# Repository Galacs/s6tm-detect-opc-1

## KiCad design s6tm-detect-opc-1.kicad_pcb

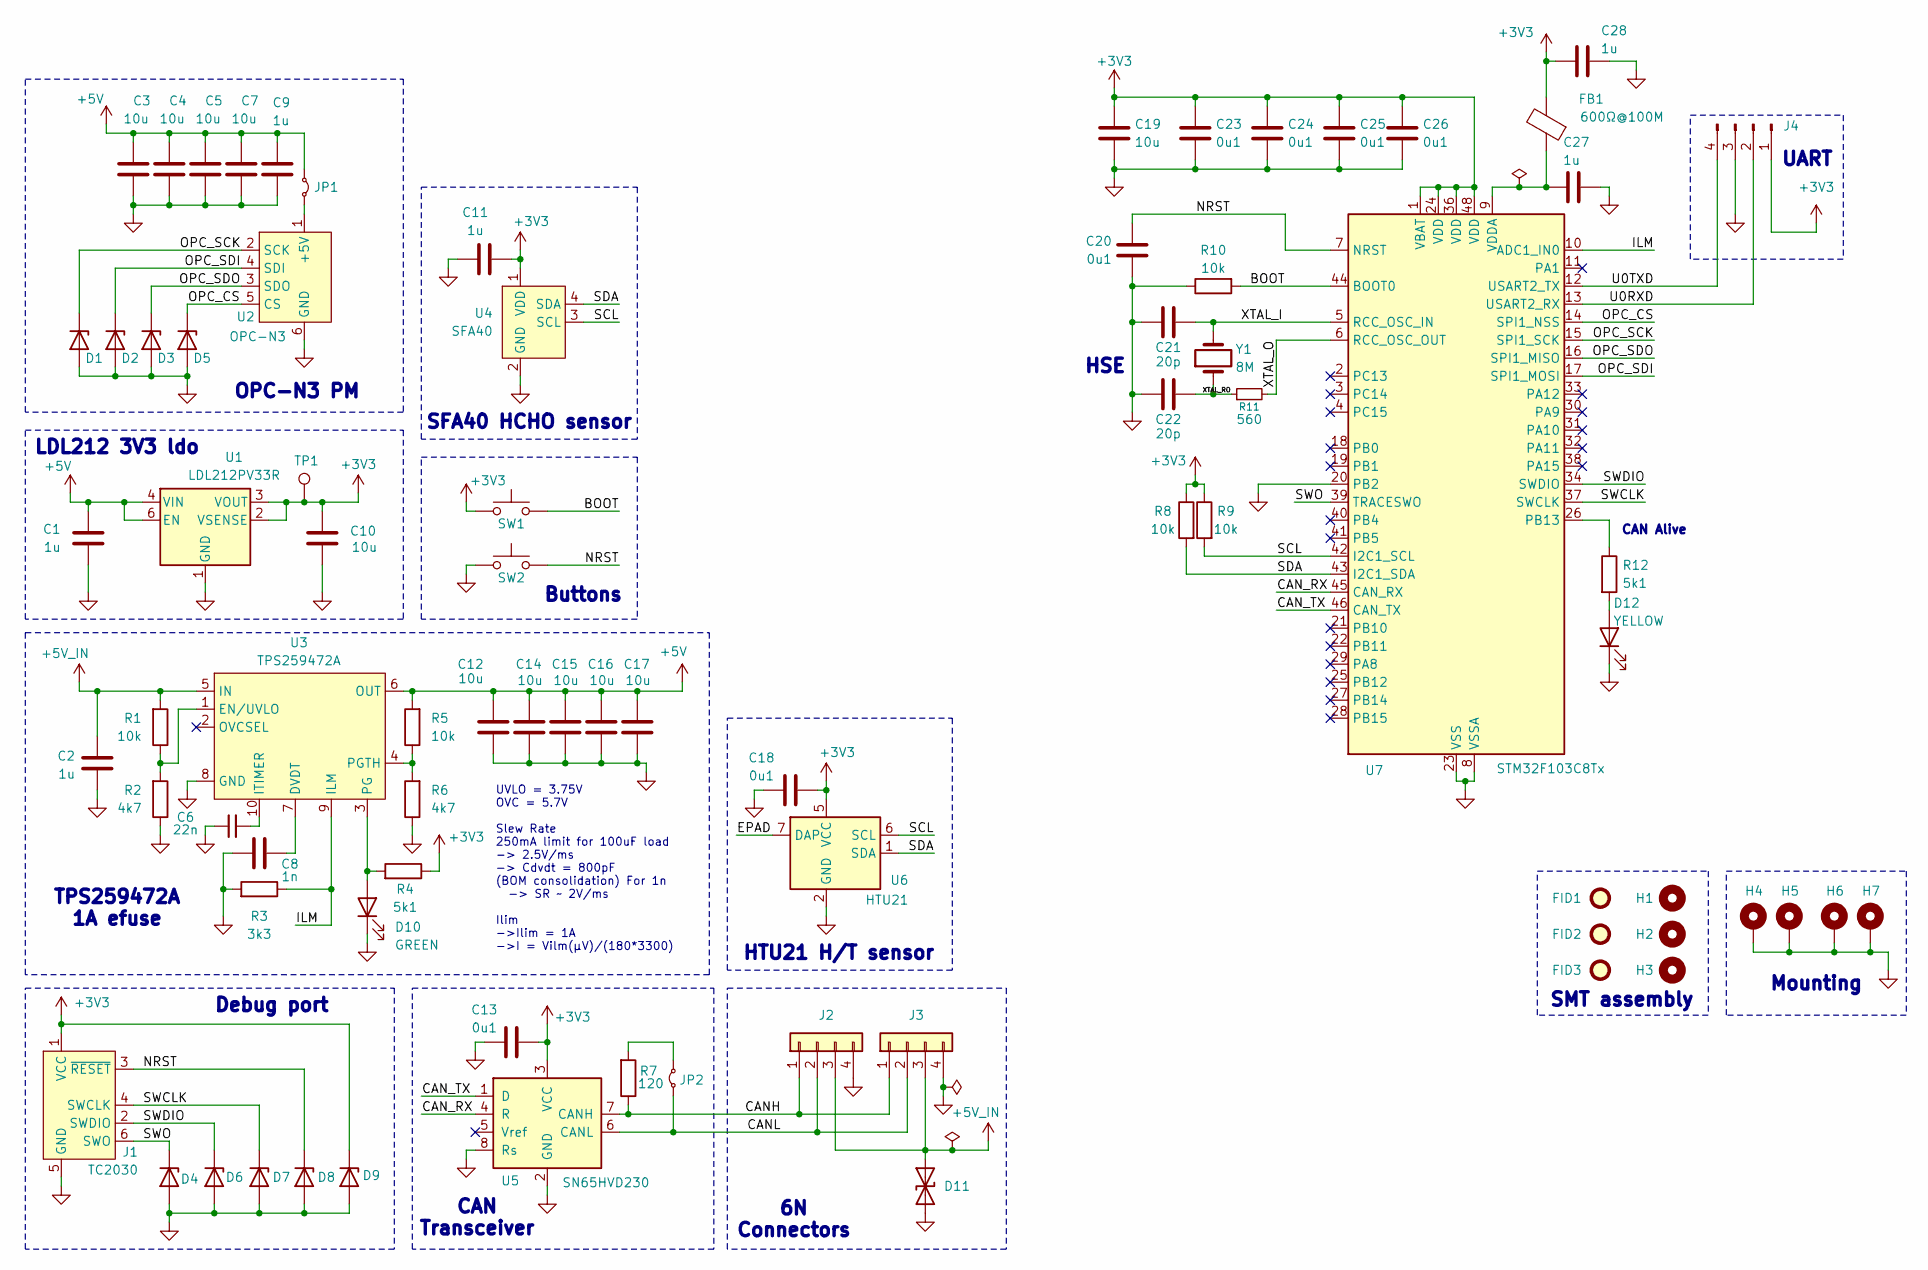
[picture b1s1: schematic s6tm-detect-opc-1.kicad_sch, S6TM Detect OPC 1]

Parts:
C1, C2, C9, C11, C27, C28: 1u; C_0402_1005Metric; Manufacturer Part Number CL05A105KA5NQNC; JLCPCB Part # C52923
C3, C4, C5, C7, C10, C12, C14, C15, C16, C17: 10u; C_0603_1608Metric; Manufacturer Part Number CL10A106KP8NNNC; JLCPCB Part # C19702
C6: 22n; C_0402_1005Metric; Manufacturer Part Number 0402B223K500NT; JLCPCB Part # C1532
C8: 1n; C_0402_1005Metric; Manufacturer Part Number 0402B102K500NT; JLCPCB Part # C1523
C13, C18, C20, C23, C24, C25, C26: 0u1; C_0402_1005Metric; Manufacturer Part Number CL05B104KB54PNC; JLCPCB Part # C307331
C19: 10u; C_0805_2012Metric; Manufacturer Part Number GRM21BR61H106KE43L; JLCPCB Part # C440198
C21, C22: 20p; C_0603_1608Metric; Manufacturer Part Number CL10C200JB8NNNC; JLCPCB Part # C1648
D1, D2, D3, D4, D5, D6, D7, D8, D9: H5VU10U; Diode_DFN1006; Manufacturer Part Number H5VU10U; JLCPCB Part # C22395519
D10: GREEN; LED_0805_2012Metric; Manufacturer Part Number KT-0805G; JLCPCB Part # C2297
D11: SMAJ6.0CA; D_SMA; Manufacturer Part Number SMAJ6.0CA; JLCPCB Part # C19077526
D12: YELLOW; LED_0805_2012Metric; Manufacturer Part Number KT-0805Y; JLCPCB Part # C2296
FB1: 600Ω@100M; L_0805_2012Metric; Manufacturer Part Number MPZ2012S601ATD25; JLCPCB Part # C81034
FID1, FID2, FID3: Fiducial; Fiducial_1mm_Mask2mm
H1, H2, H3: MountingHole; ToolingHole_1.152mm
H4, H5, H6, H7: MountingHole_Pad; MountingHole_3.2mm_M3_Pad_Via
J1: TC2030; Tag-Connect_TC2030-IDC-NL_2x03_P1.27mm_Vertical
J2, J3: Conn_01x04; JST_XH_S4B-XH-A-1_1x04_P2.50mm_Horizontal; Manufacturer Part Number S4B-XH-A-1(LF)(SN); JLCPCB Part # C163037
J4: Conn_01x04_Pin; PinHeader_1x04_P2.54mm_Vertical
JP1, JP2: Jumper_2_Small_Bridged; PinHeader_1x02_P2.54mm_Vertical
R1, R5, R8, R9, R10: 10k; R_0402_1005Metric; Manufacturer Part Number 0402WGF1002TCE; JLCPCB Part # C25744
R2, R6: 4k7; R_0402_1005Metric; Manufacturer Part Number 0402WGF4701TCE; JLCPCB Part # C25900
R3: 3k3; R_0402_1005Metric; Manufacturer Part Number 0402WGF3301TCE; JLCPCB Part # C25890
R4, R12: 5k1; R_0402_1005Metric; Manufacturer Part Number 0402WGF5101TCE; JLCPCB Part # C25905
R7: 120; R_1206_3216Metric; Manufacturer Part Number 1206W4F1200T5E; JLCPCB Part # C17909
R11: 560; R_0603_1608Metric; Manufacturer Part Number 0603WAF5600T5E; JLCPCB Part # C23204
SW1, SW2: SW_Push; SW_SPST_TS-1088-xR020; Manufacturer Part Number TS-1088-AR02016; JLCPCB Part # C720477
TP1: TestPoint; TestPoint_Pad_D2.0mm
U1: LDL212PV33R; DFN-6-1EP_2x2mm_P0.5mm_ST; Manufacturer Part Number LDL212PV33R; JLCPCB Part # C2969892
U2: OPC-N3; Molex_Pico-Clasp_202396-0607_1x06-1MP_P1.00mm_Horizontal; Manufacturer Part Number 5015680607; JLCPCB Part # C505000
U3: TPS259472A; Texas_RPW0010A_VQFN-HR-10_2x2mm_P0.5mm; Manufacturer Part Number TPS259472ARPWR; JLCPCB Part # C3662789
U4: SFA40; Sensirion_SFA40
U5: SN65HVD230; SOIC-8_3.9x4.9mm_P1.27mm; Manufacturer Part Number SN65HVD230DR; JLCPCB Part # C12084
U6: HTU21; Texas_PWSON-N6; Manufacturer Part Number HTU21D; JLCPCB Part # C83479
U7: STM32F103C8Tx; LQFP-48_7x7mm_P0.5mm; Manufacturer Part Number STM32F103C8T6; JLCPCB Part # C8734
Y1: 8M; Crystal_SMD_5032-2Pin_5.0x3.2mm; Manufacturer Part Number X50328MSB2GI; JLCPCB Part # C115962

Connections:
+3V3: C10.1, C11.2, C13.1, C18.2, C19.1, C23.1, C24.1, C25.1, C26.1, C28.1, D9.1 (K), FB1.2, J1.1 (VCC), J4.1, R4.1, R8.1, R9.1, SW1.1, TP1.1 (1_1), U1.2 (VSENSE), U1.3 (VOUT), U4.1 (VDD), U5.3 (VCC), U6.5 (VCC), U7.1 (VBAT), U7.24 (VDD), U7.36 (VDD), U7.48 (VDD)
+5V_IN: C2.2, D11.1 (A1), J2.3, J3.3, R1.2, U3.5 (IN)
/BOOT: R10.2, SW1.2, U7.44 (BOOT0)
/CANH: J2.1, J3.1, R7.1, U5.7 (CANH)
/CANL: J2.2, J3.2, JP2.1 (A), U5.6 (CANL)
/CAN_RX: U5.4 (R), U7.45 (CAN_RX)
/CAN_TX: U5.1 (D), U7.46 (CAN_TX)
/EPAD: U6.7 (DAP)
/ILM: R3.1, U3.9 (ILM), U7.10 (ADC1_IN0)
/NRST: C20.1, D8.1 (K), J1.3 (~RESET), SW2.2, U7.7 (NRST)
/OPC_CS: D5.1 (K), U2.5 (CS), U7.14 (SPI1_NSS)
/OPC_SCK: D1.1 (K), U2.2 (SCK), U7.15 (SPI1_SCK)
/OPC_SDI: D2.1 (K), U2.4 (SDI), U7.17 (SPI1_MOSI)
/OPC_SDO: D3.1 (K), U2.3 (SDO), U7.16 (SPI1_MISO)
/SCL: R9.2, U4.3 (SCL), U6.6 (SCL), U7.42 (I2C1_SCL)
/SDA: R8.2, U4.4 (SDA), U6.1 (SDA), U7.43 (I2C1_SDA)
/SWCLK: D7.1 (K), J1.4 (SWCLK), U7.37 (SWCLK)
/SWDIO: D6.1 (K), J1.2 (SWDIO), U7.34 (SWDIO)
/SWO: D4.1 (K), J1.6 (SWO), U7.39 (TRACESWO)
/U0RXD: J4.2, U7.13 (USART2_RX)
/U0TXD: J4.4, U7.12 (USART2_TX)
/XTAL_I: C21.1, U7.5 (RCC_OSC_IN), Y1.2
/XTAL_O: R11.2, U7.6 (RCC_OSC_OUT)
/XTAL_RO: C22.1, R11.1, Y1.1
GND: C1.2, C2.1, C3.2, C4.2, C5.2, C6.2, C7.2, C8.2, C9.1, C10.2, C11.1, C12.2, C13.2, C14.2, C15.2, C16.2, C17.2, C18.1, C19.2, C20.2, C21.2, C22.2, C23.2, C24.2, C25.2, C26.2, C27.2, C28.2, D1.2 (A), D2.2 (A), D3.2 (A), D4.2 (A), D5.2 (A), D6.2 (A), D7.2 (A), D8.2 (A), D9.2 (A), D10.1 (K), D11.2 (A2), D12.1 (K), H4.1 (1_1), H5.1 (1_1), H6.1 (1_1), H7.1 (1_1), J1.5 (GND), J2.4, J3.4, J4.3, R2.1, R3.2, R6.1, R10.1, SW2.1, U1.1 (GND), U2.6 (GND), U3.8 (GND), U4.2 (GND), U4.6 (GND), U5.2 (GND), U5.8 (Rs), U6.2 (GND), U7.8 (VSSA), U7.20 (PB2), U7.23 (VSS), U7.35 (VSS), U7.47 (VSS)
unnamed: D10.2 (A), R4.2, U3.3 (PG)
unnamed: D12.2 (A), R12.2
unnamed: JP2.2 (B), R7.2
unnamed: C8.1, U3.7 (DVDT)
unnamed: R1.1, R2.2, U3.1 (EN/UVLO)
unnamed: C6.1, U3.10 (ITIMER)
unnamed: R5.1, R6.2, U3.4 (PGTH)
unnamed: R12.1, U7.26 (PB13)
unnamed: C27.1, FB1.1, U7.9 (VDDA)

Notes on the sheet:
Buttons
OPC-N3 PM
UVLO = 3.75V OVC = 5.7V Slew Rate 250mA limit for 100uF load -> 2.5V/ms -> Cdvdt = 800pF (BOM consolidation) For 1n -> SR ~ 2V/ms Ilim ->Ilim = 1A ->I = Vilm(µV)/(180*3300)
TPS259472A 1A efuse
UART
Mounting
SMT assembly
LDL212 3V3 ldo
CAN Transceiver
HSE
SFA40 HCHO sensor
Debug port
CAN Alive
6N Connectors
HTU21 H/T sensor

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
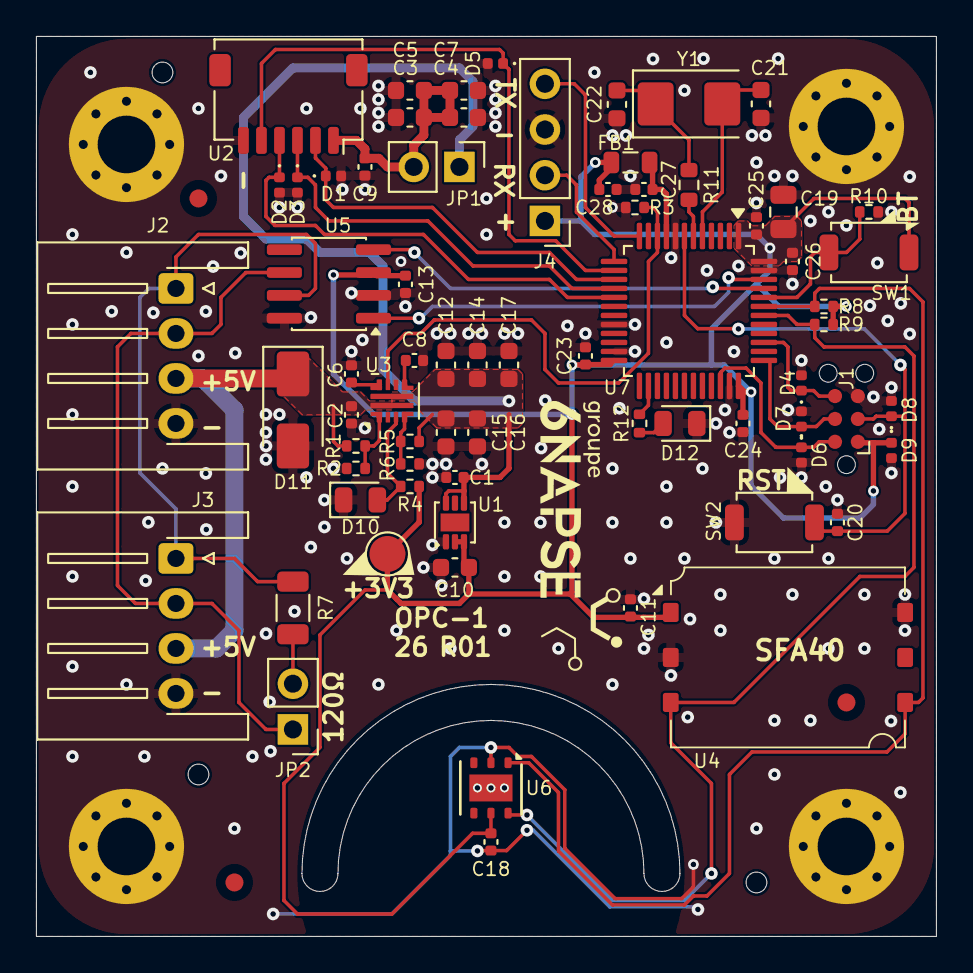
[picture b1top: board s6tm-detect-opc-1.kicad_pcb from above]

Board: 2 copper layers, 50.0 x 50.0 mm, 80 parts (0 on the bottom side), 34 nets.

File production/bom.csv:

Designator,Footprint,Quantity,Value,LCSC Part #
"C1, C11, C2, C27, C28, C9",0402,6,1u,C52923
"C10, C12, C14, C15, C16, C17, C3, C4, C5, C7",0603,10,10u,C19702
"C13, C18, C20, C23, C24, C25, C26",0402,7,0u1,C307331
C19,0805,1,10u,C440198
"C21, C22",0603,2,20p,C1648
C6,0402,1,22n,C1532
C8,0402,1,1n,C1523
"D1, D2, D3, D4, D5, D6, D7, D8, D9",Diode_DFN1006,9,H5VU10U,C22395519
D10,0805,1,GREEN,C2297
D11,D_SMA,1,SMAJ6.0CA,C19077526
D12,0805,1,YELLOW,C2296
FB1,0805,1,600Ω@100M,C81034
"J2, J3",JST_XH_S4B-XH-A-1_1x04_P2.50mm_Horizontal,2,Conn_01x04,C163037
"R1, R10, R5, R8, R9",0402,5,10k,C25744
R11,0603,1,560,C23204
"R12, R4",0402,2,5k1,C25905
"R2, R6",0402,2,4k7,C25900
R3,0402,1,3k3,C25890
R7,1206,1,120,C17909
"SW1, SW2",SW_SPST_TS-1088-xR020,2,SW_Push,C720477
U1,DFN-6-1EP_2x2mm_P0.5mm_ST,1,LDL212PV33R,C2969892
U2,Molex_Pico-Clasp_202396-0607_1x06-1MP_P1.00mm_Horizontal,1,OPC-N3,C505000
U3,Texas_RPW0010A_VQFN-HR-10_2x2mm_P0.5mm,1,TPS259472A,C3662789
U5,SOIC-8_3.9x4.9mm_P1.27mm,1,SN65HVD230,C12084
U6,Texas_PWSON-N6,1,HTU21,C83479
U7,LQFP-48_7x7mm_P0.5mm,1,STM32F103C8Tx,C8734
Y1,Crystal_SMD_5032-2Pin_5.0x3.2mm,1,8M,C115962
